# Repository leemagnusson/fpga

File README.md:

# fpga

Hobby FPGA projects, mostly targeting a Basys 3 board (Artix-7 `xc7a35tcpg236-1`).

| Directory    | What it is                                                     | Build                    |
|--------------|----------------------------------------------------------------|--------------------------|
| `bml1/ch4`   | LED shift register built from UNISIM primitives (VHDL + Verilog) | `cd bml1/ch4 && ./go.sh` |
| `bml1/ch5`   | Same design in behavioural RTL with a 1 Hz pulse               | `cd bml1/ch5 && ./go.sh` |
| `bml1/seg`, `bml1/seg2` | Seven-segment display, switches and buttons (`seg2` counts button presses per second) | `cd bml1/seg2 && ./go.sh` |
| `can_timing` | CAN message timing model and `can_sim` testbench (sim only)    | Vivado project `can_timing/project_1` |
| `litefury_canfd` | CAN FD PCIe card on a LiteFury, SocketCAN via the mainline driver | `cd litefury_canfd && ./go.sh` (see its README) |
| `t1s_trigger` | 10BASE-T1S bus monitor with switch-selected scope trigger outputs, plus the KiCad tap Pmod | `cd t1s_trigger && ./go.sh` (see its README) |
| `src`        | Early BCD counter experiments (not currently building)         |                          |

`go.sh` runs `go.tcl` in Vivado batch mode: synthesis, place, route, reports,
bitstream, then `program.tcl` to load the board over JTAG. Set the `CI`
environment variable to skip the programming step:

```sh
CI=1 ./go.sh
```

## Continuous integration

Two GitHub Actions workflows live in `.github/workflows/`.

### `ci.yml` (runs everywhere, no setup)

Runs on GitHub-hosted runners in the `hdlc/ghdl:yosys` container and executes
`ci/check.sh`, which:

- synthesises `bml1/ch4` and `bml1/ch5` for Artix-7 with GHDL + Yosys
  (both the VHDL and the Verilog top), catching syntax, elaboration and
  non-synthesisable-construct errors;
- runs the `can_timing` testbench in GHDL for 2 ms;
- analyses the loose tutorial files in `bml1/`.

`ci/unisim_stub.vhd` provides behavioural stand-ins for the UNISIM primitives
used by `bml1/ch4` so GHDL can build it. The same script runs locally with:

```sh
docker run --rm -v "$PWD":/src -w /src hdlc/ghdl:yosys ci/check.sh
```

### `vivado.yml` (real Vivado flow, needs a self-hosted runner)

Vivado cannot run on GitHub-hosted runners, so this workflow runs each
project's `go.tcl` on a self-hosted runner, checks that `top.bit` was produced
and that timing was met, and uploads the bitstream and reports as artifacts.
Pull requests from forks never run on the self-hosted runner.

All Vivado invocations go through `ci/vivado.sh`, which runs Vivado natively
or inside a Docker image depending on the environment. It works on a dev
machine too:

```sh
cd bml1/ch5
../../ci/vivado.sh -mode batch -source go.tcl                                           # native
VIVADO_DOCKER_IMAGE=vivado-runtime:2026.1 ../../ci/vivado.sh -mode batch -source go.tcl   # Docker
```

#### Setting up a runner machine

A fresh Linux machine with sudo is enough. Four steps:

1. **Download the Vivado web installer** on that machine into `~/Downloads`:
   the Linux "Self Extracting Web Installer" (about 400 MB, AMD login
   required) from
   https://www.amd.com/en/support/downloads/adaptive-socs-and-fpgas/development-tools.html

2. **Get a runner registration token** from the repo on GitHub: Settings,
   Actions, Runners, "New self-hosted runner", then copy the value from the
   `./config.sh --token ...` line. It is a short-lived code for adding one
   runner, not a personal access token, and it expires after an hour, so
   fetch it right before step 3. With the `gh` CLI logged in:

   ```sh
   gh api -X POST repos/leemagnusson/fpga/actions/runners/registration-token --jq .token
   ```

3. **Run the bootstrap** on the machine:

   ```sh
   curl -fsSL https://raw.githubusercontent.com/leemagnusson/fpga/main/ci/runner/bootstrap.sh \
     | bash -s -- --token <registration token>
   ```

   It installs Docker and a few tools, clones this repo to `~/fpga`, installs
   a minimal Vivado (Artix-7 only, about 20 GB) to `~/Xilinx` from the web
   installer, builds the small `vivado-runtime` Docker image, and registers
   and starts the runner service with the `vivado` label. Expect three
   prompts: the sudo password, your AMD account e-mail and password (used
   once to create the installer's download token), and sudo again for the
   runner service. The Vivado download is the slow part. At the end the
   installer prints the machine's host ID for the next step.

4. **Licence and switch on.** Vivado 2026.1 needs its free BASIC licence
   file even for Artix-7, and it is node-locked, so each machine needs its
   own. Generate one for the printed host ID at the AMD licensing site and
   save it on the runner as `~/.Xilinx/Xilinx.lic`. Then set the repository
   variable `VIVADO_RUNNER` to `true` on GitHub (Settings, Secrets and
   variables, Actions, Variables) and push a commit or run the "Vivado
   build" workflow manually.

If the machine already has Vivado on its PATH, the bootstrap skips the
install and uses it. `ci/runner/install.sh --help` and
`ci/vivado-install/install.sh --help` describe the individual pieces for
doing it by hand.

#### Installing Vivado from the web, scripted

`ci/vivado-install/install.sh` drives the AMD web installer in batch mode and
installs the smallest useful Vivado: the 2026.1 "Vivado Design Suite" edition
with only the Artix-7 family, no DocNav, no Model Composer, no shortcuts. The
only manual parts are downloading the web installer and typing your AMD
account once.

```sh
ci/vivado-install/install.sh --installer ~/Downloads/FPGAs_AdaptiveSoCs_Unified_SDI_2026.1_*_Lin64.bin
```

Options: `--dest` (default `~/Xilinx`), `--devices "Artix-7 FPGAs,Spartan-7 FPGAs"`
(see `--list-devices` for the names), `--cable-drivers` for machines that
program boards, `--prepare-only` to stop after writing the config. For a
runner that should keep Vivado inside Docker instead of on the host,
`ci/docker/build.sh --web <installer>` runs the same install during an
image build; the installer comes in as a build context and the AMD token
as a build secret, so neither is stored in the image.

#### Option A: Vivado in Docker (recommended)

The runner machine needs Docker, with the runner's user in the `docker`
group. Build the image once on the runner:

```sh
ci/docker/build.sh
```

This builds `vivado-runtime:<version>`, a small Ubuntu 24.04 image with
Vivado's runtime libraries and locale. Vivado itself stays on the host and is
bind-mounted read-only into the container at run time, so nothing licensed is
copied into an image and there is no AMD installer or auth token to deal
with. The install root is found from `vivado` on PATH, or set `VIVADO_HOME`.
Because the container is Ubuntu 24.04, the `libncurses.so.5` start-up failure
on newer host distributions does not occur.

Vivado 2026.1 needs its free BASIC license file even for WebPACK parts. The
wrapper mounts `~/.Xilinx/Xilinx.lic` into the container automatically, or
set `VIVADO_LICENSE_FILE` to point at it. The container uses the host network
so a node-locked license still matches the host ID.

Then put `VIVADO_DOCKER_IMAGE=vivado-runtime:2026.1` in the runner's `.env`
file (per machine), or set it as a repository variable (applies to every
runner and overrides `.env`).

#### Option B: Vivado natively on the runner

Make sure `vivado` is on the runner service's `PATH`, or set the repository
variable `VIVADO_SETTINGS` to the path of Vivado's `settings64.sh`.

Note for Ubuntu newer than 24.04: Vivado 2026.1 does not recognise the OS and
fails at start-up with `libncurses.so.5: cannot open shared object file`,
while still exiting 0. Point it at its own bundled copy, for example in the
runner's `.env` file:

```sh
LD_LIBRARY_PATH=<vivado-install>/Vivado/lib/lnx64.o/Ubuntu/24
```

On such an OS Vivado also spills part of `/etc/os-release` into the comment
banner of every HDL file it generates, which breaks synthesis of block
designs with `syntax error near 'VERSION_ID'`. `litefury_canfd/go.tcl`
repairs the generated files (see `litefury_canfd/fix_banners.tcl`); the
other projects generate no HDL and are unaffected.

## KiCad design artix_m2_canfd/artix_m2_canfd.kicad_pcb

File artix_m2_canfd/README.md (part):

# artix_m2_canfd: M.2 2280 Artix-7 card with four CAN FD transceivers

A 22 x 80 mm M.2 key-M card (PCIe x4 Gen2) around an AMD Artix-7 XC7A50T
with four CAN FD transceivers, intended to run the `litefury_canfd` design
in this repo extended to four cores. The whole KiCad project is generated
by `gen/build.py`; edit the Python, not the KiCad files.

```
python3 gen/build.py          # regenerates *.kicad_sch, *.kicad_pcb, lib/, bom.csv
```

## Design

| Block | Part | Notes |
|---|---|---|
| FPGA | XC7A50T-2CSG325I | 15 x 15 mm, 0.8 mm BGA, 4 GTP transceivers. The XC7A35T (and smaller) in CSG325 is a drop-in; the 75T and 100T are not offered in CSG325 (DS180 table 5), and only CSG325 has GTPs and fits the 22 mm card |
| Host interface | M.2 2280 key M card edge | PCIe x4 to GTP bank 216, REFCLK AC-coupled to MGTREFCLK0, PERST# to an I/O, CLKREQ# tied low |
| CAN FD | 4 x MCP2542FD (DFN-8; MCP2562FD, MCP2558FD and TI TCAN1462V are pin-compatible) | 8 Mbit/s, 5 V supply with 3.3 V I/O, ESD diode and optional 120 ohm termination (DNP) per bus |
| CAN connectors | 2 x Hirose DF52-6S-0.8H | 1.5 mm high, at the far end either side of the mount notch; each carries two buses as CANH, CANL, GND |
| Configuration | W25Q128JV (WSON-8), QSPI x4, M[2:0] = 001 | Tag-Connect TC2050 pads for JTAG, no connector |
| Clock | 100 MHz 3.3 V oscillator (ECS-2520MV) on an MRCC pin | 200 MHz LVDS not needed; the FPGA design's clock wizard takes 100 MHz |
| VCCINT/VCCBRAM 1.0 V | TPS62823 buck, 3 A | first rail up |
| VCCAUX 1.8 V | TLV62569 buck, 2 A | enabled by the 1.0 V power-good |
| MGTAVCC 1.0 V, MGTAVTT 1.2 V | TLV75710 / TLV75512 LDOs from 1.8 V (TLV755xP and TLV757xP share a pinout) | low noise for the transceivers |
| VCCO 3.3 V | TPS22918 load switch from the M.2 3.3 V | enabled ~10 ms after 1.8 V, slew limited: gives the recommended VCCINT, VCCAUX, VCCO order |
| 5 V (CAN) | TPS61023 boost from 3.3 V | enabled with the 3.3 V rail |
| LEDs | 4 user (bank 34) + power | active low, 0402 |

The FPGA pin assignment is generated from the AMD package file
(`gen/data/xc7a50tcsg325pkg.txt`): PCIe lanes reversed on the GTP
channels, user I/O (12 CAN signals, 4 LEDs) on bank 34, the oscillator and
PERST# on bank 15 clock-capable pins, QSPI on the bank 14 configuration
pins. All I/O banks run at 3.3 V.

Stackup: 6 layers, 0.8 mm (M.2 requirement), signal / ground / power /
power / ground / signal, ENIG. The 0.8 mm BGA fans out with 0.2/0.45 mm
vias on the pad diagonals and 0.1 mm traces.

### M.2 pin mapping

From the PCIe M.2 specification rev 1.0, table 48 (socket 3, key M) and
figures 16/17. The table names pins from the host's side: `PETp/n` is the
host transmitter, so it connects to the FPGA receivers, and `PERp/n` (host
receiver) is driven by the FPGA transmitters through 100 nF AC coupling
capacitors on the card. REFCLK is AC coupled too. Pins 59-66 are the key.
The card-edge geometry (0.5 mm pitch, 38 top pads 2.0 mm long, 37 bottom
pads 2.5 mm long staggered by 0.25 mm, fingers centred on the 19.85 mm
wide connector tongue, pin 1 at the right in the top view, key slot
1.2 x 3.5 mm next to pin 75, 3.5 mm semicircular mount notch centred on
the far edge) is in `gen/footprints.py` (`M2_*` constants) and the outline
in `gen/pcb.py`.

## Routing flow

The generator places parts and draws the planes; `gen/route.py` then does
all the copper itself (no external autorouter):

```sh
python3 gen/build.py                 # regenerate schematic, board, libraries (stops if a part does not fit its zone)
python3 gen/route.py route           # BGA escapes, plane vias, gen/router.py for everything else,
                                     #   then KiCad's DRC in a loop until it reports nothing (about 2 minutes)
kicad-cli pcb drc --severity-all artix_m2_canfd.kicad_pcb     # 0 violations, 0 unconnected
```

`gen/escape.py` takes every used BGA ball to a via one pitch outside the
package: outer ring straight out on the top layer, second ring through the
free row gap, deeper balls on the bottom layer along the pad-row/column
lines. The receive pairs are planned as pairs and leave the bottom row in
M.2 finger order (lane 0 west ... lane 3 east), REFCLK between lanes 0 and
1. `gen/fanout.py` adds a via to its plane beside every supply pad.

`gen/router.py` is a grid router (0.1 mm lattice, A* over F.Cu and B.Cu)
that works in this order:

1. **PCIe pairs** as pairs: one search for the centreline, P and N offset
   0.125 mm either side (0.1 mm tracks, 0.15 mm gap), symmetric lead-ins,
   via pairs at a layer change, 0.3 mm kept to the next pair. Receive pairs
   run straight to the fingers on F.Cu; the transmit pairs come down the east
   edge on B.Cu, cross under the receive pairs and surface at their
   capacitors. Each pair is then length-matched with small bumps on the
   shorter half (all within 0.1 mm; the 1.6 mm that the ring-1/ring-2
   transmit balls differ by inside the package is made up outside it).
2. **Supplies**: pads the fan-out could not stitch, and the two
   transceiver-rail corner islands under the GTP balls, are joined to their
   planes.
3. **Local power links**: every regulator and transceiver supply pin goes
   straight to its capacitor or inductor on the same layer with the fattest
   track that fits (exact geometry, 0.25-0.8 mm), switch nodes included, so
   no decoupling loop runs through two vias and a plane.
4. **Signals**, short nets first, with rip-up and retry.
5. KiCad's DRC is run on the saved board; anything it reports (a via the
   plane fill did not reach, a track a few microns close to a round pad) is
   mended and the DRC run again until it is clean.

Planes (6 layers, 0.8 mm): L2 and L5 ground. L3 is 3.3 V from the package
upwards; below it and along the two long edges L3 carries the transceiver
rails (MGTAVCC west, MGTAVTT east), each a strip from its LDO down to a
block under its decoupling, plus the island under the GTP balls that the
router links to the block. L4 is 1.8 V with a 1.0 V strip from the core
balls up to the buck, the 3.3 V input under the fingers and up both long
edges to the regulators, and 5 V at the CAN end. A 0.3 mm keep-out ring
keeps routed copper off the board edge.

### PCIe lane and polarity assignment (matters for the FPGA constraints)

The M.2 lanes are **reversed** on the GTP quad and the **transmit pairs
are polarity-swapped**, so that nothing has to cross on the board:

| M.2 lane | GTP channel | RX balls (P/N) | TX balls carrying PERp/PERn |
|---|---|---|---|
| 0 | 3 (MGTP*3_216) | G4 / G3 | B1 (MGTPTXN3) / B2 (MGTPTXP3) |
| 1 | 2 | C4 / C3 | D1 (MGTPTXN2) / D2 (MGTPTXP2) |
| 2 | 1 | A4 / A3 | F1 (MGTPTXN1) / F2 (MGTPTXP1) |
| 3 | 0 | E4 / E3 | H1 (MGTPTXN0) / H2 (MGTPTXP0) |

`python3 gen/xdc.py` writes the Vivado constraints for all FPGA pins from
the routed board into `../litefury_canfd/constraints/artix_m2*.xdc` (build
with `BOARD=artix_m2`, see that README); `--check` reports drift. It places
lane n's GTPE2_CHANNEL on channel 3-n with a LOC constraint.
The transmit polarity needs nothing: the host's receivers detect and
correct an inverted lane during link training (PCIe base spec, lane
polarity inversion). REFCLK is on MGTREFCLK0 (D6/D5), not inverted.

## Fabrication and assembly

### PCBWay

```sh
python3 gen/pcbway.py            # build/pcbway/artix_m2_canfd.zip: gerbers, drills, IPC-356 netlist,
                                 #   BOM, pick-and-place, fab notes (PCBWay's plugin format)
python3 gen/pcbway.py --upload   # ... and upload it; prints and opens the PCBWay quote page
python3 gen/pcbway.py --quote    # price table for the options in PCB_SPEC (needs PCBWAY_API_KEY)
python3 gen/pcbway.py --order 10 # ten boards with those options into your PCBWay cart (needs the key)
```

`gen/pcbway.py` writes the same package as PCBWay's KiCad plugin and uses
the same anonymous upload endpoint, so the quote page comes up with the
files attached; log in there, pick the options the script prints (6 layers,
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
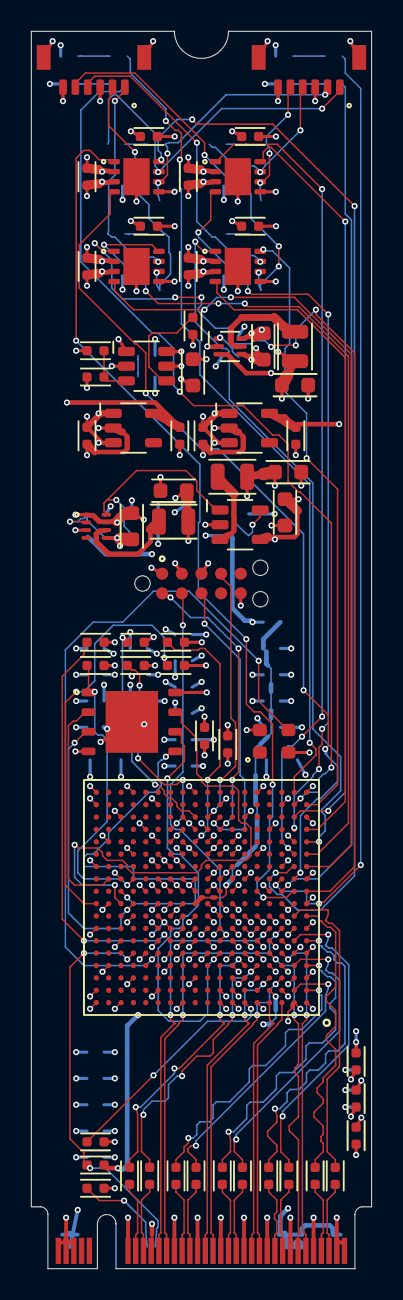
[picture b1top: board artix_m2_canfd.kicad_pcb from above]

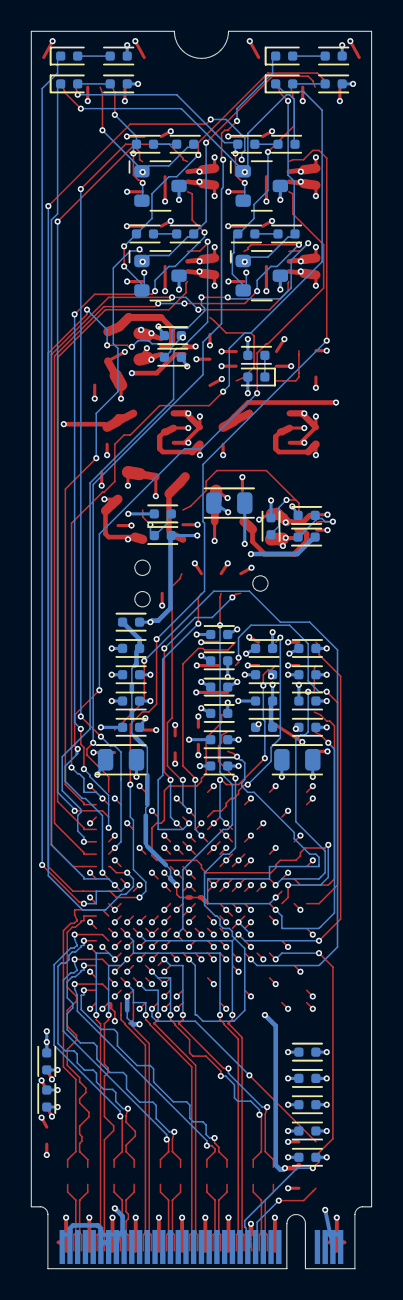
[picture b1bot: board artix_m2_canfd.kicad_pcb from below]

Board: 6 copper layers, 22.0 x 80.0 mm, 124 parts (58 on the bottom side), 98 nets.

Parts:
C1, C2, C3, C4, C5, C6, C7, C8, C9, C10, C11, C12, C34, C35, C36, C37, C38, C39, C42, C52, C57, C58, C59, C60, C61, C62, C63, C64: 100n; C_0402
C13, C14, C20, C24, C25, C26, C27, C32, C33, C40, C41: 4u7; C_0402
C15, C16, C17, C18, C21, C22, C28, C29, C30, C31: 470n; C_0402
C19, C23, C45: 47u; C_0805
C43, C46, C54, C55, C56: 10u; C_0603
C44, C47: 22u; C_0603
C48, C49, C50, C51: 1u; C_0402
C53: 1n; C_0402
D1, D2, D3, D4, D5: LED green; LED_0402
D10, D11, D12, D13: PESD2CAN; SOT-23
FB1: 600R@100MHz; FB_0402
J1: M.2 2280 key M; M2_Edge_2280_KeyM
J2: TC2050 JTAG; TagConnect_TC2050-NL
J3, J4: DF52-6S-0.8H; Hirose_DF52-6S-0.8H
L1: 470nH; L_0806
L2, L3: 1uH; L_0806
R1, R24, R26, R28, R30: 0R; R_0402
R2: 10k; R_0402
R3: 100R; R_0402
R4, R5, R6, R7, R8, R9: 4k7; R_0402
R10, R11, R12, R13, R20: 1k; R_0402
R14: 68k; R_0402
R15, R16, R18, R19, R22: 100k; R_0402
R17: 200k; R_0402
R21: 732k; R_0402
R23, R25, R27, R29: 120R; R_0402
U1: XC7A50T-2CSG325I; Xilinx_CSG325
U2: W25Q128JVPIQ; WSON-8_6x5mm_P1.27mm
U3: TPS62823DLCR; VSON-8_2x1.5mm_P0.5mm
U4: TLV62569DBVR; SOT-23-5
U5: TLV75710PDBVR; SOT-23-5
U6: TLV75512PDBVR; SOT-23-5
U7: TPS22918DBVR; SOT-23-6
U8: TPS61023DRLR; SOT-563
U10, U11, U12, U13: MCP2542FD; DFN-8_3x3mm_P0.65mm
X1: 100 MHz 3.3V; Oscillator_2520_4pin

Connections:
CAN0_H: D10.1, J3.1, R23.1, U10.7
CAN0_L: D10.2, J3.2, R24.2, U10.6
CAN0_RXD: U1.M1, U10.4
CAN0_STBY: U1.N1, U10.8
CAN0_TERM: R23.2, R24.1
CAN0_TXD: U1.K1, U10.1
CAN1_H: D11.1, J3.4, R25.1, U11.7
CAN1_L: D11.2, J3.5, R26.2, U11.6
CAN1_RXD: U1.R1, U11.4
CAN1_STBY: U1.U1, U11.8
CAN1_TERM: R25.2, R26.1
CAN1_TXD: U1.P1, U11.1
CAN2_H: D12.1, J4.1, R27.1, U12.7
CAN2_L: D12.2, J4.2, R28.2, U12.6
CAN2_RXD: U1.L2, U12.4
CAN2_STBY: U1.M2, U12.8
CAN2_TERM: R27.2, R28.1
CAN2_TXD: U1.K2, U12.1
CAN3_H: D13.1, J4.4, R29.1, U13.7
CAN3_L: D13.2, J4.5, R30.2, U13.6
CAN3_RXD: U1.R2, U13.4
CAN3_STBY: U1.T2, U13.8
CAN3_TERM: R29.2, R30.1
CAN3_TXD: U1.N2, U13.1
CFG_M0: R5.1, U1.R12
CLK100M: U1.E13, X1.3
CT_3V3: C53.1, U7.4
DONE: R7.1, U1.F12
EN_3V3: C52.1, R19.2, U7.3
FB_1V0: R14.2, R15.1, U3.2
FB_1V8: R17.2, R18.1, U4.5
FB_5V: R21.2, R22.1, U8.1
GND: C11.2, C12.2, C13.2, C14.2, C15.2, C16.2, C17.2, C18.2, C19.2, C20.2, C21.2, C22.2, C23.2, C24.2, C25.2, C26.2, C27.2, C28.2, C29.2, C30.2, C31.2, C32.2, C33.2, C34.2, C35.2, C36.2, C37.2, C38.2, C39.2, C40.2, C41.2, C42.2, C43.2, C44.2, C45.2, C46.2, C47.2, C48.2, C49.2, C50.2, C51.2, C52.2, C53.2, C54.2, C55.2, C56.2, C57.2, C58.2, C59.2, C60.2, C61.2, C62.2, C63.2, C64.2, D10.3, D11.3, D12.3, D13.3, J1.1, J1.3, J1.9, J1.15, J1.21, J1.27, J1.33, J1.39, J1.45, J1.51, J1.57, J1.71, J1.73, J1.75, J2.3, J2.5, J2.10, J3.3, J3.6, J3.MP, J4.3, J4.6, J4.MP, R1.2, R3.2, R15.2, R18.2, R20.2, R22.2, U1.A1, U1.A5, U1.A7, U1.A8, U1.A11, U1.A18, U1.B3, U1.B7, U1.B8, U1.B18, U1.C2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
INIT_B: R8.1, U1.T10
JTAG_TCK: J2.4, U1.F8
JTAG_TDI: J2.7, U1.T9
JTAG_TDO: J2.6, U1.T8
JTAG_TMS: J2.2, U1.R8
LED0_A: D1.2, R10.1
LED0_N: D1.1, U1.U2
LED1_A: D2.2, R11.1
LED1_N: D2.1, U1.V2
LED2_A: D3.2, R12.1
LED2_N: D3.1, U1.K3
LED3_A: D4.2, R13.1
LED3_N: D4.1, U1.L3
MGTAVCC: C32.1, C33.1, C34.1, C35.1, C36.1, C49.1, U1.B4, U1.C5, U1.E5, U1.F5, U5.5
MGTAVTT: C37.1, C38.1, C39.1, C40.1, C41.1, C51.1, U1.A2, U1.C1, U1.E1, U1.F3, U1.G2, U6.5
MGTRREF: R3.1, U1.A6
PCIE_CLKREQ_N: J1.52, R1.1
PCIE_PERST_N: J1.50, R2.1, U1.E15
PCIE_REFCLK_N: C10.1, U1.D5
PCIE_REFCLK_N_C: C10.2, J1.53
PCIE_REFCLK_P: C9.1, U1.D6
PCIE_REFCLK_P_C: C9.2, J1.55
PCIE_RX0_N: J1.47, U1.G3
PCIE_RX0_P: J1.49, U1.G4
PCIE_RX1_N: J1.35, U1.C3
PCIE_RX1_P: J1.37, U1.C4
PCIE_RX2_N: J1.23, U1.A3
PCIE_RX2_P: J1.25, U1.A4
PCIE_RX3_N: J1.11, U1.E3
PCIE_RX3_P: J1.13, U1.E4
PCIE_TX0_N: C2.1, U1.B2
PCIE_TX0_N_C: C2.2, J1.41
PCIE_TX0_P: C1.1, U1.B1
PCIE_TX0_P_C: C1.2, J1.43
PCIE_TX1_N: C4.1, U1.D2
PCIE_TX1_N_C: C4.2, J1.29
PCIE_TX1_P: C3.1, U1.D1
PCIE_TX1_P_C: C3.2, J1.31
PCIE_TX2_N: C6.1, U1.F2
PCIE_TX2_N_C: C6.2, J1.17
PCIE_TX2_P: C5.1, U1.F1
PCIE_TX2_P_C: C5.2, J1.19
PCIE_TX3_N: C8.1, U1.H2
PCIE_TX3_N_C: C8.2, J1.5
PCIE_TX3_P: C7.1, U1.H1
PCIE_TX3_P_C: C7.2, J1.7
PG_1V0: R16.1, U3.8, U4.1
PROGRAM_B: R9.1, U1.P10
PUDC_B: R6.1, U1.J18
PWR_LED_K: D5.1, R20.1
QSPI_CLK: U1.E8, U2.6
QSPI_CS_N: R4.1, U1.L15, U2.1
QSPI_IO0: U1.K16, U2.5
QSPI_IO1: U1.L17, U2.2
QSPI_IO2: U1.J15, U2.3
QSPI_IO3: U1.J16, U2.7
SW_1V0: L1.1, U3.6
SW_1V8: L2.1, U4.3
SW_5V: L3.2, U8.5
VCC1V0: C13.1, C14.1, C15.1, C16.1, C17.1, C18.1, C44.1, C45.1, L1.2, R14.1, U1.F7, U1.F9, U1.F11, U1.G8, U1.G10, U1.H7, U1.H9, U1.H11, U1.J8, U1.J12, U1.K7, U1.K11, U1.L8, U1.L12, U1.M7, U1.M11, U1.N8, U1.N10, U1.N12, U1.P9, U1.P11
VCC1V8: C19.1, C20.1, C21.1, C22.1, C47.1, C48.1, C50.1, FB1.1, L2.2, R17.1, R19.1, U1.E11, U1.G12, U1.H13, U1.K13, U1.M13, U1.P13, U5.1, U5.3, U6.1, U6.3
VCC3V3: C11.1, C12.1, C23.1, C24.1, C25.1, C26.1, C27.1, C28.1, C29.1, C30.1, C31.1, C54.1, C58.1, C60.1, C62.1, C64.1, D5.2, J2.1, R2.2, R4.2, R5.2, R6.2, R7.2, R8.2, R9.2, R10.2, R11.2, R12.2, R13.2, U1.A16, U1.B13, U1.C10, U1.D17, U1.E10, U1.E12, U1.E14, U1.G18, U1.H15, U1.L6, U1.L16, U1.M3, U1.P7, U1.P17, U1.R4, U1.R10, U1.R14, U1.T1, U1.T11, U1.U8, U1.U18, U1.V5, U1.V15, U2.8, U7.5, U7.6, U8.2, U10.5, U11.5, U12.5, U13.5, X1.4
VCC5V_CAN: C56.1, C57.1, C59.1, C61.1, C63.1, R21.1, U8.6, U10.3, U11.3, U12.3, U13.3
VCCADC: C42.1, FB1.2, U1.J10
VIN_3V3: C43.1, C46.1, C55.1, J1.2, J1.4, J1.12, J1.14, J1.16, J1.18, J1.70, J1.72, J1.74, L3.1, R16.2, U3.1, U3.7, U4.4, U7.1, U8.3

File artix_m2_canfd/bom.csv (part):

Reference,Value,MPN,Footprint,Description,DNP
C1,"100n","GRM155R71C104KA88D","artix_m2_canfd:C_0402","Capacitor 100n 16V 0402",
C2,"100n","GRM155R71C104KA88D","artix_m2_canfd:C_0402","Capacitor 100n 16V 0402",
C3,"100n","GRM155R71C104KA88D","artix_m2_canfd:C_0402","Capacitor 100n 16V 0402",
C4,"100n","GRM155R71C104KA88D","artix_m2_canfd:C_0402","Capacitor 100n 16V 0402",
C5,"100n","GRM155R71C104KA88D","artix_m2_canfd:C_0402","Capacitor 100n 16V 0402",
C6,"100n","GRM155R71C104KA88D","artix_m2_canfd:C_0402","Capacitor 100n 16V 0402",
C7,"100n","GRM155R71C104KA88D","artix_m2_canfd:C_0402","Capacitor 100n 16V 0402",
C8,"100n","GRM155R71C104KA88D","artix_m2_canfd:C_0402","Capacitor 100n 16V 0402",
C9,"100n","GRM155R71C104KA88D","artix_m2_canfd:C_0402","Capacitor 100n 16V 0402",
C10,"100n","GRM155R71C104KA88D","artix_m2_canfd:C_0402","Capacitor 100n 16V 0402",
C11,"100n","GRM155R71C104KA88D","artix_m2_canfd:C_0402","Capacitor 100n  0402",
C12,"100n","GRM155R71C104KA88D","artix_m2_canfd:C_0402","Capacitor 100n  0402",
C13,"4u7","GRM155R60J475ME47D","artix_m2_canfd:C_0402","Capacitor 4u7  0402",
C14,"4u7","GRM155R60J475ME47D","artix_m2_canfd:C_0402","Capacitor 4u7  0402",
C15,"470n","GRM155R61A474KE15D","artix_m2_canfd:C_0402","Capacitor 470n  0402",
C16,"470n","GRM155R61A474KE15D","artix_m2_canfd:C_0402","Capacitor 470n  0402",
C17,"470n","GRM155R61A474KE15D","artix_m2_canfd:C_0402","Capacitor 470n  0402",
C18,"470n","GRM155R61A474KE15D","artix_m2_canfd:C_0402","Capacitor 470n  0402",
C19,"47u","GRM21BR60J476ME15L","artix_m2_canfd:C_0805","Capacitor 47u  0805",
C20,"4u7","GRM155R60J475ME47D","artix_m2_canfd:C_0402","Capacitor 4u7  0402",
C21,"470n","GRM155R61A474KE15D","artix_m2_canfd:C_0402","Capacitor 470n  0402",
C22,"470n","GRM155R61A474KE15D","artix_m2_canfd:C_0402","Capacitor 470n  0402",
C23,"47u","GRM21BR60J476ME15L","artix_m2_canfd:C_0805","Capacitor 47u  0805",
C24,"4u7","GRM155R60J475ME47D","artix_m2_canfd:C_0402","Capacitor 4u7  0402",
C25,"4u7","GRM155R60J475ME47D","artix_m2_canfd:C_0402","Capacitor 4u7  0402",
C26,"4u7","GRM155R60J475ME47D","artix_m2_canfd:C_0402","Capacitor 4u7  0402",
C27,"4u7","GRM155R60J475ME47D","artix_m2_canfd:C_0402","Capacitor 4u7  0402",
C28,"470n","GRM155R61A474KE15D","artix_m2_canfd:C_0402","Capacitor 470n  0402",
C29,"470n","GRM155R61A474KE15D","artix_m2_canfd:C_0402","Capacitor 470n  0402",
C30,"470n","GRM155R61A474KE15D","artix_m2_canfd:C_0402","Capacitor 470n  0402",
C31,"470n","GRM155R61A474KE15D","artix_m2_canfd:C_0402","Capacitor 470n  0402",
C32,"4u7","GRM155R60J475ME47D","artix_m2_canfd:C_0402","Capacitor 4u7  0402",
C33,"4u7","GRM155R60J475ME47D","artix_m2_canfd:C_0402","Capacitor 4u7  0402",
C34,"100n","GRM155R71C104KA88D","artix_m2_canfd:C_0402","Capacitor 100n  0402",
C35,"100n","GRM155R71C104KA88D","artix_m2_canfd:C_0402","Capacitor 100n  0402",
C36,"100n","GRM155R71C104KA88D","artix_m2_canfd:C_0402","Capacitor 100n  0402",
C37,"4u7","GRM155R60J475ME47D","artix_m2_canfd:C_0402","Capacitor 4u7  0402",
C38,"4u7","GRM155R60J475ME47D","artix_m2_canfd:C_0402","Capacitor 4u7  0402",
C39,"100n","GRM155R71C104KA88D","artix_m2_canfd:C_0402","Capacitor 100n  0402",
C40,"100n","GRM155R71C104KA88D","artix_m2_canfd:C_0402","Capacitor 100n  0402",
C41,"100n","GRM155R71C104KA88D","artix_m2_canfd:C_0402","Capacitor 100n  0402",
C42,"100n","GRM155R71C104KA88D","artix_m2_canfd:C_0402","Capacitor 100n  0402",
C43,"10u","GRM188R61A106KE69D","artix_m2_canfd:C_0603","Capacitor 10u 10V 0603",
C44,"22u","GRM188R60J226MEA0D","artix_m2_canfd:C_0603","Capacitor 22u 6.3V 0603",
C45,"47u","GRM21BR60J476ME15L","artix_m2_canfd:C_0805","Capacitor 47u 6.3V 0805",
C46,"10u","GRM188R61A106KE69D","artix_m2_canfd:C_0603","Capacitor 10u 10V 0603",
C47,"22u","GRM188R60J226MEA0D","artix_m2_canfd:C_0603","Capacitor 22u 6.3V 0603",
C48,"1u","GRM155R61A105KE15D","artix_m2_canfd:C_0402","Capacitor 1u 10V 0402",
C49,"1u","GRM155R61A105KE15D","artix_m2_canfd:C_0402","Capacitor 1u 10V 0402",
C50,"1u","GRM155R61A105KE15D","artix_m2_canfd:C_0402","Capacitor 1u 10V 0402",
C51,"1u","GRM155R61A105KE15D","artix_m2_canfd:C_0402","Capacitor 1u 10V 0402",
C52,"100n","GRM155R71C104KA88D","artix_m2_canfd:C_0402","Capacitor 100n  0402",
C53,"1n","GRM1555C1H102JA01D","artix_m2_canfd:C_0402","Capacitor 1n  0402",
C54,"10u","GRM188R61A106KE69D","artix_m2_canfd:C_0603","Capacitor 10u 10V 0603",
C55,"10u","GRM188R61A106KE69D","artix_m2_canfd:C_0603","Capacitor 10u 10V 0603",
C56,"10u","GRM188R61A106KE69D","artix_m2_canfd:C_0603","Capacitor 10u 10V 0603",
C57,"100n","GRM155R71C104KA88D","artix_m2_canfd:C_0402","Capacitor 100n  0402",
C58,"100n","GRM155R71C104KA88D","artix_m2_canfd:C_0402","Capacitor 100n  0402",
C59,"100n","GRM155R71C104KA88D","artix_m2_canfd:C_0402","Capacitor 100n  0402",
C60,"100n","GRM155R71C104KA88D","artix_m2_canfd:C_0402","Capacitor 100n  0402",
C61,"100n","GRM155R71C104KA88D","artix_m2_canfd:C_0402","Capacitor 100n  0402",
C62,"100n","GRM155R71C104KA88D","artix_m2_canfd:C_0402","Capacitor 100n  0402",
C63,"100n","GRM155R71C104KA88D","artix_m2_canfd:C_0402","Capacitor 100n  0402",
C64,"100n","GRM155R71C104KA88D","artix_m2_canfd:C_0402","Capacitor 100n  0402",
D1,"LED green","16-213/GHC-YR1S1/3T","artix_m2_canfd:LED_0402","LED green 0402",
D2,"LED green","16-213/GHC-YR1S1/3T","artix_m2_canfd:LED_0402","LED green 0402",
D3,"LED green","16-213/GHC-YR1S1/3T","artix_m2_canfd:LED_0402","LED green 0402",
D4,"LED green","16-213/GHC-YR1S1/3T","artix_m2_canfd:LED_0402","LED green 0402",
D5,"LED green","16-213/GHC-YR1S1/3T","artix_m2_canfd:LED_0402","LED green 0402",
D10,"PESD2CAN","PESD2CAN,215","artix_m2_canfd:SOT-23","CAN bus ESD protection",
D11,"PESD2CAN","PESD2CAN,215","artix_m2_canfd:SOT-23","CAN bus ESD protection",
D12,"PESD2CAN","PESD2CAN,215","artix_m2_canfd:SOT-23","CAN bus ESD protection",
D13,"PESD2CAN","PESD2CAN,215","artix_m2_canfd:SOT-23","CAN bus ESD protection",
FB1,"600R@100MHz","BLM15AG601SN1D","artix_m2_canfd:FB_0402","Ferrite bead 0402",
J1,"M.2 2280 key M","","artix_m2_canfd:M2_Edge_2280_KeyM","M.2 card edge, 2280, key M (PCIe x4 + 3.3 V)",
J2,"TC2050 JTAG","","artix_m2_canfd:TagConnect_TC2050-NL","Tag-Connect TC2050 JTAG pads, no part fitted (cable TC2050-IDC-NL; Xilinx: VREF, TMS, GND, TCK, GND, TDO, TDI)",
J3,"DF52-6S-0.8H","DF52-6S-0.8H(21)","artix_m2_canfd:Hirose_DF52-6S-0.8H","CAN buses 0 and 1: H, L, GND each; 0.8 mm wire-to-board, 1.5 mm tall",
J4,"DF52-6S-0.8H","DF52-6S-0.8H(21)","artix_m2_canfd:Hirose_DF52-6S-0.8H","CAN buses 2 and 3: H, L, GND each; 0.8 mm wire-to-board, 1.5 mm tall",
L1,"470nH","TFM201610ALMA-R47MTAA","artix_m2_canfd:L_0806","Inductor 470nH 2016",
L2,"1uH","TFM201610ALMA-1R0MTAA","artix_m2_canfd:L_0806","Inductor 1uH 2016",
L3,"1uH","TFM201610ALMA-1R0MTAA","artix_m2_canfd:L_0806","Inductor 1uH 2016",
R1,"0R","RC0402JR-070RL","artix_m2_canfd:R_0402","Resistor 0R 0402",
R2,"10k","RC0402FR-0710KL","artix_m2_canfd:R_0402","Resistor 10k 0402",
R3,"100R","RC0402FR-07100RL","artix_m2_canfd:R_0402","Resistor 100R 0402",
R4,"4k7","RC0402FR-074K7L","artix_m2_canfd:R_0402","Resistor 4k7 0402",
R5,"4k7","RC0402FR-074K7L","artix_m2_canfd:R_0402","Resistor 4k7 0402",
R6,"4k7","RC0402FR-074K7L","artix_m2_canfd:R_0402","Resistor 4k7 0402",
R7,"4k7","RC0402FR-074K7L","artix_m2_canfd:R_0402","Resistor 4k7 0402",
R8,"4k7","RC0402FR-074K7L","artix_m2_canfd:R_0402","Resistor 4k7 0402",
R9,"4k7","RC0402FR-074K7L","artix_m2_canfd:R_0402","Resistor 4k7 0402",
R10,"1k","RC0402FR-071KL","artix_m2_canfd:R_0402","Resistor 1k 0402",
R11,"1k","RC0402FR-071KL","artix_m2_canfd:R_0402","Resistor 1k 0402",
R12,"1k","RC0402FR-071KL","artix_m2_canfd:R_0402","Resistor 1k 0402",
R13,"1k","RC0402FR-071KL","artix_m2_canfd:R_0402","Resistor 1k 0402",
R14,"68k","RC0402FR-0768KL","artix_m2_canfd:R_0402","Resistor 68k 0402",
R15,"100k","RC0402FR-07100KL","artix_m2_canfd:R_0402","Resistor 100k 0402",
R16,"100k","RC0402FR-07100KL","artix_m2_canfd:R_0402","Resistor 100k 0402",
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
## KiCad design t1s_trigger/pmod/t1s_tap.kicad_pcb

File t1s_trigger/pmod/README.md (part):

# 10BASE-T1S tap Pmod

A small Pmod module that lets the Basys 3 listen to a 10BASE-T1S bus and
brings four trigger outputs to connectors. KiCad 9 project, two layers,
20 x 46 mm.

```
T1S bus (A/B) --> J2 screw terminal / J3 header --> U1 RS-485 receiver -------------> RX  --> Pmod IO1  (low: line negative)
                                   |---------------> U2 RS-485 receiver, A/B swapped --> RXN --> Pmod IO10 (low: line positive)
                                   |- JP1 (shunt) + R1: optional 100 R termination
FPGA TRIG0..3 --> Pmod IO2,IO3,IO4,IO7 --> 33 R --> J5 header; TRIG0 also --> 49.9 R --> J4 SMA
```

The receivers are 3.3 V, 50 Mbit/s RS-485 transceivers used receive-only:
high-impedance differential inputs with a wide common-mode range and a
fail-safe output (idle bus reads as logic 1), which is what a passive monitor
tap needs. The 10BASE-T1S differential Manchester signal has at most one edge
every 40 ns, well inside a 50 Mbit/s part. There are two of them because one
cannot tell idle from positive: the fail-safe thresholds sit at about -20 and
-200 mV, so the output only changes when the line crosses about -0.1 V. U2 has
A and B swapped and so only reacts to crossings of about +0.1 V. Together they
give the FPGA three states, negative (RX low), positive (RXN low) and idle
(both high), and every transition on the wire, including the first one out of
idle whichever polarity it has, asserts exactly one of the two outputs. U1's
driver is held off by R4 unless the FPGA drives IO8 high; `IO9` is the driver
data pin so the board can inject test patterns if you ever want to (not T1S
compliant levels). U2's driver pins are grounded.

## Files

| File | What |
|------|------|
| `t1s_tap.kicad_pro`, `t1s_tap.kicad_sch`, `t1s_tap.kicad_pcb` | the KiCad 9 project |
| `t1s_tap.kicad_sym`, `sym-lib-table` | project symbol library (transceiver symbol) |
| `tools/netlist.py` | the circuit as data: parts, footprints, pin to net. Schematic and board are both generated from it |
| `tools/gen_sch.py`, `tools/gen_pcb.py` | generators (schematic as s-expressions, board through the pcbnew API) |
| `tools/build.sh` | regenerates everything and runs ERC, DRC, schematic parity, a pad/net cross-check and all exports |
| `tools/pcbway_quote.sh` | uploads the gerber zip (or, with `assembly`, gerbers + BOM + placement) to PCBWay and prints a link to a pre-filled instant quote |
| `tools/pcbway_files.py` | writes `out/PCBWay_bom.csv`, `out/PCBWay_positions.csv` (the layout PCBWay's KiCad plugin uses) and `out/t1s_tap_assembly.zip` |
| `3dmodels/` | STEP models for every part (copied from kicad-packages3D, CC-BY-SA 4.0); the board references them as `${KIPRJMOD}/3dmodels/` so the 3D view works without the global library |
| `out/` | ERC and DRC reports (JSON), schematic PDF/SVG, board SVG and PNG renders, 3D renders (`pcb_3d.png`, `pcb_3d_rear.png`), `t1s_tap.step` (board with components, for mechanical checks), `bom.csv` (with manufacturer part numbers), `positions.csv`, `gerbers/`, `t1s_tap_gerbers.zip` and `t1s_tap_assembly.zip` |

Everything runs in the `kicad/kicad:9.0` Docker image, no local KiCad needed:

```sh
tools/build.sh
```

## Pmod pinout (J1)

Standard 12-pin Pmod, 3.3 V. Pmod pins 1 to 6 are the upper row, 7 to 12 the
lower row. Looking at the module with the header pointing away from you and
components up, pin 1 is at the **right** end of the upper row and pin 6 at the
left (Digilent Pmod Interface Specification 1.3.1, figure 2; Basys 3 reference
manual figure 20 shows the matching socket, front view, pin 1 top right). The
KiCad footprint numbers its pads the other way round, pad 1 at the left in that
view, so `tools/netlist.py` maps Pmod pin *n* to pad 13-2*n* (pins 1 to 6) and
26-2*n* (pins 7 to 12), and `gen_pcb.py` moves the square pad and the pin-1
tick to Pmod pin 1. Rev A had the header mirrored; plugged into a Basys 3 it
would have put 3.3 V and ground on JA signal pins.

| Pmod pin | Signal | Direction (FPGA) | Note |
|---------:|--------|------------------|------|
| 1 (IO1)  | RX     | in  | U1 output: low while the line is negative, idles high |
| 2 (IO2)  | TRIG0  | out | to J5 pin 1 via 33 R and to J4 SMA via 49.9 R |
| 3 (IO3)  | TRIG1  | out | to J5 pin 2 via 33 R |
| 4 (IO4)  | TRIG2  | out | to J5 pin 3 via 33 R |
| 5        | GND    |     | |
| 6        | VCC    |     | 3.3 V from the host |
| 7 (IO7)  | TRIG3  | out | to J5 pin 4 via 33 R |
| 8 (IO8)  | DE     | out | driver enable, 10 k pull-down, leave low or unused |
| 9 (IO9)  | TXD    | out | driver data (only matters with DE high) |
| 10 (IO10)| RXN    | in  | U2 output: low while the line is positive, idles high |
| 11       | GND    |     | |
| 12       | VCC    |     | 3.3 V |

On the Basys 3 header JA this is JA1 = RX, JA2 = TRIG0, JA3 = TRIG1,
JA4 = TRIG2, JA7 = TRIG3, JA8 = DE, JA9 = TXD, JA10 = RXN.

**Check pin 1 before plugging in.** The silkscreen marks Pmod pin 1 (square
pad with a tick) and pins 6, 7 and 12 at the row ends. Hold the module next to
the Basys 3 JA socket and confirm the square pad lines up with the socket's
pin 1 (the Basys 3 silkscreen marks it); the right-angle header can be soldered
on either face, and a module plugged in upside down puts 3.3 V on signal pins.

## Other connectors

| Ref | What | Pins |
|-----|------|------|
| J2  | 3.5 mm screw terminal | 1 = A, 2 = B (10BASE-T1S pair) |
| J3  | 1x3 0.1" header, same bus in parallel | 1 = A, 2 = B, 3 = GND |
| J4  | SMA, edge mount | TRIG0 through 49.9 R, use a 50 R scope input or a 1 M input (then you get the full 3.3 V) |
| J5  | 1x5 0.1" header | 1 = TRIG0, 2 = TRIG1, 3 = TRIG2, 4 = TRIG3, 5 = GND, each through 33 R |
| JP1 | 1x2 0.1" header + shunt | shunt fitted: 100 R (R1) across A/B. Ship without the shunt |
| D1  | green LED | lit while the bus is active (RX low), dark when silent |

## Bill of materials

| Ref | Value | Package | Example part | Notes |
|-----|-------|---------|--------------|-------|
| U1, U2 | SN65HVD78 | SOIC-8 | TI SN65HVD78D | 3.3 V, 50 Mbps, fail-safe RS-485. Alternatives with the same pinout: ADI ADM3065EARZ, Maxim MAX22500EASA. Do not fit a 5 V-only or 500 kbps part. Fit the same part in both places |
| C1, C2 | 100 nF | 0603 | any X7R 16 V | decoupling |
| R1 | 100 R | 0603 | 1 % | termination, only with JP1 closed |
| R2 | 49.9 R | 0603 | 1 % | SMA source termination |
| R3 | 1 k | 0603 | | LED |
| R4 | 10 k | 0603 | | DE pull-down |
| R5 to R8 | 33 R | 0603 | | trigger series resistors |
| D1 | green | 0603 LED | | activity |
| J1 | 2x6 right-angle male 0.1" | | e.g. Sullins PRPC006DBAN-M71 or any 2x6 right angle | Pmod plug |
| J2 | 2-pos 3.5 mm screw terminal | | Phoenix PT 1,5/2-3,5-H (1984617) | bus |
| J3 | 1x3 male 0.1" | | | bus, header |
| J4 | SMA edge mount | | Amphenol 132289 | TRIG0 |
| J5 | 1x5 male 0.1" | | | triggers |
| JP1 | 1x2 male 0.1" | | Sullins PRPC002SAAN-RC plus a 2.54 mm shunt, e.g. Sullins SPC02SYAN | termination select |

`out/bom.csv` is the machine-generated version (the shunt for JP1 is a loose
part and not in it).

## Assembly and use

- **Keep the stub short.** 10BASE-T1S nodes hang off the mixing segment on
  stubs of a few centimetres at most. Wire J2 or J3 to the bus with the
  shortest twisted pair you can, ideally directly at a bus connector or at
  the end node. The tap adds roughly 30 pF (two receiver inputs) plus the
  stub to the bus.
- **Termination.** A 10BASE-T1S mixing segment has exactly two 100 R
  terminations, one at each end; everything else hangs off it on short stubs.
  Leave the JP1 shunt off unless this module *is* one end of the bus on your
  bench, then fit it. A third termination in the middle halves the signal and
  reflects.
- **Coupling.** Real nodes sit on the bus through 100 nF series capacitors
  on both wires (Microchip AN1718 bus interface network, OPEN Alliance
  10BASE-T1S implementation specification), and the end terminations are
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
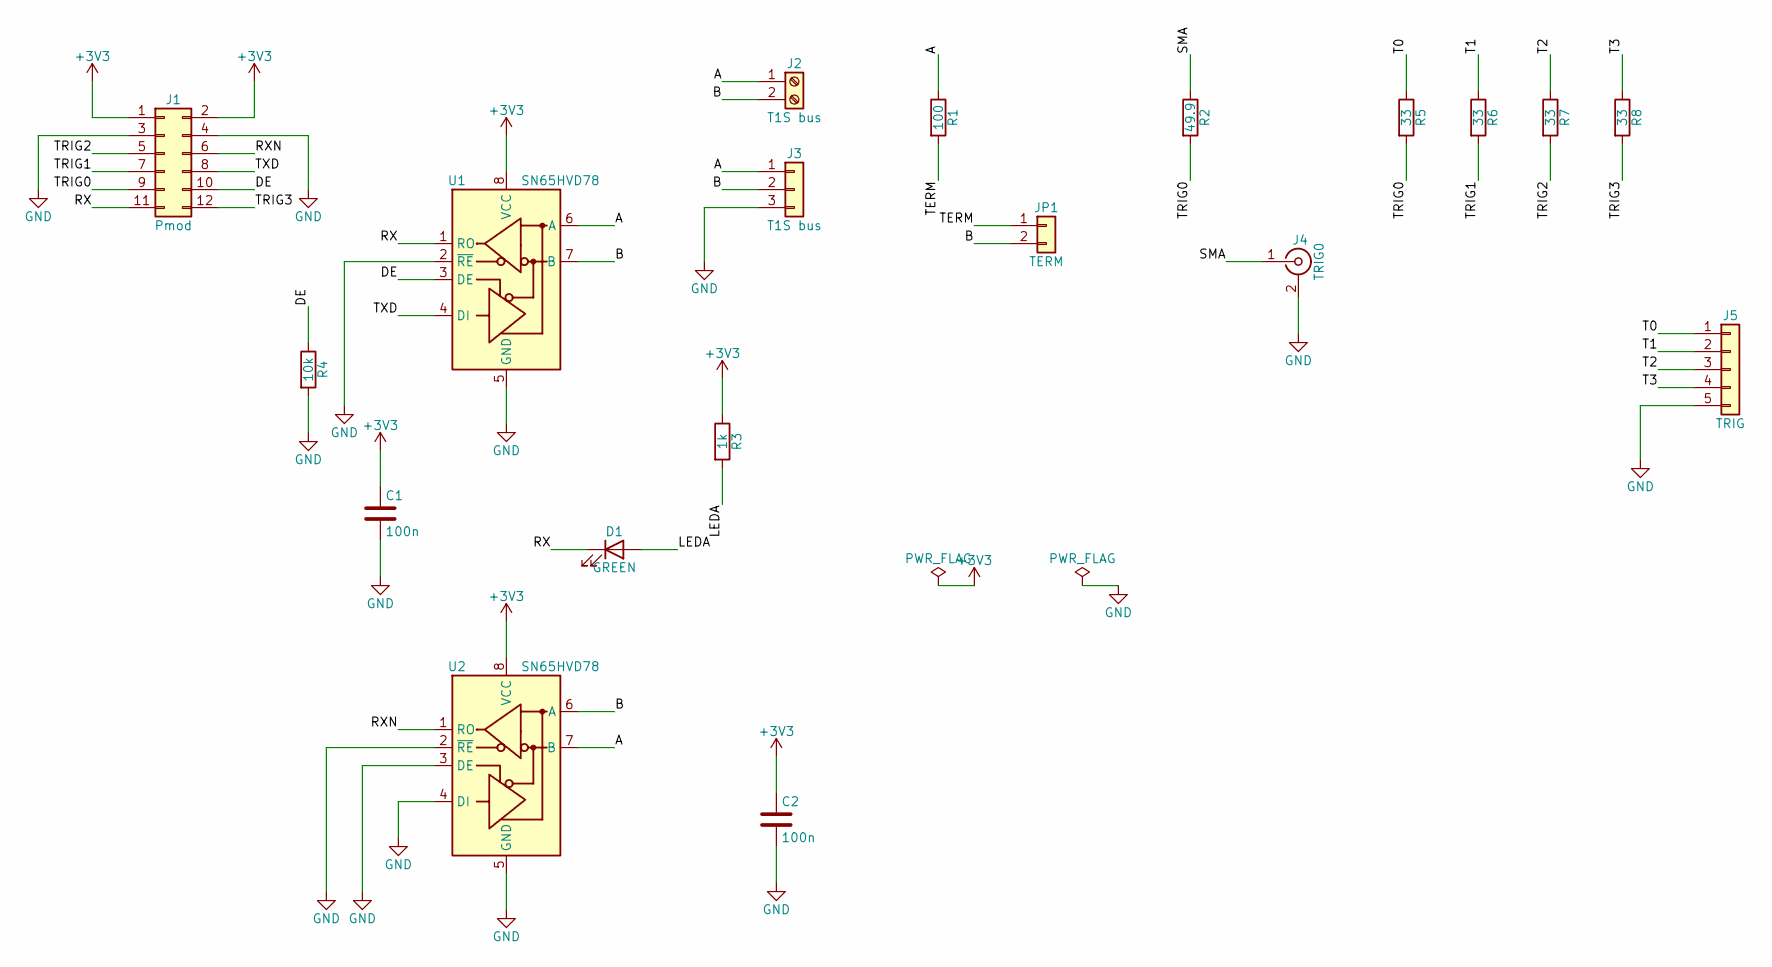
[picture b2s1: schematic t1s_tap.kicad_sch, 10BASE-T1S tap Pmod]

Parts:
C1, C2: 100n; C_0603_1608Metric; MPN CC0603KRX7R9BB104
D1: GREEN; LED_0603_1608Metric; MPN APT1608SGC
J1: Pmod; PinHeader_2x06_P2.54mm_Horizontal; MPN PRPC006DBAN-M71
J2: T1S bus; TerminalBlock_Phoenix_PT-1,5-2-3.5-H_1x02_P3.50mm_Horizontal; MPN 1984617
J3: T1S bus; PinHeader_1x03_P2.54mm_Vertical; MPN PRPC003SAAN-RC
J4: TRIG0; SMA_Amphenol_132289_EdgeMount; MPN 132289
J5: TRIG; PinHeader_1x05_P2.54mm_Vertical; MPN PRPC005SAAN-RC
JP1: TERM; PinHeader_1x02_P2.54mm_Vertical; MPN PRPC002SAAN-RC
R1: 100; R_0603_1608Metric; MPN RC0603FR-07100RL
R2: 49.9; R_0603_1608Metric; MPN RC0603FR-0749R9L
R3: 1k; R_0603_1608Metric; MPN RC0603FR-071KL
R4: 10k; R_0603_1608Metric; MPN RC0603FR-0710KL
R5, R6, R7, R8: 33; R_0603_1608Metric; MPN RC0603FR-0733RL
U1, U2: SN65HVD78; SOIC-8_3.9x4.9mm_P1.27mm; MPN SN65HVD78D

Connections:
+3V3: C1.1, C2.1, J1.1, J1.2, R3.1, U1.8 (VCC), U2.8 (VCC)
/A: J2.1, J3.1, R1.1, U1.6 (A), U2.7 (B)
/B: J2.2, J3.2, JP1.2, U1.7 (B), U2.6 (A)
/DE: J1.10, R4.1, U1.3 (DE)
/LEDA: D1.2 (A), R3.2
/RX: D1.1 (K), J1.11, U1.1 (RO)
/RXN: J1.6, U2.1 (RO)
/SMA: J4.1 (In), R2.1
/T0: J5.1, R5.1
/T1: J5.2, R6.1
/T2: J5.3, R7.1
/T3: J5.4, R8.1
/TERM: JP1.1, R1.2
/TRIG0: J1.9, R2.2, R5.2
/TRIG1: J1.7, R6.2
/TRIG2: J1.5, R7.2
/TRIG3: J1.12, R8.2
/TXD: J1.8, U1.4 (DI)
GND: C1.2, C2.2, J1.3, J1.4, J3.3, J4.2 (Ext), J5.5, R4.2, U1.2 (~RE), U1.5 (GND), U2.2 (~RE), U2.3 (DE), U2.4 (DI), U2.5 (GND)

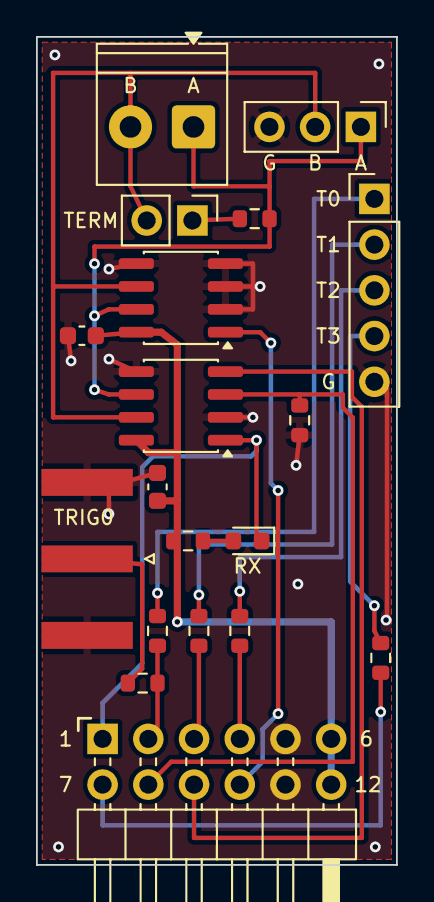
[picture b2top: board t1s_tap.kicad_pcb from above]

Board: 2 copper layers, 20.0 x 46.0 mm, 19 parts (0 on the bottom side), 19 nets.

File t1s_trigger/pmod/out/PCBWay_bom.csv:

Designator,Quantity,Value,Footprint,Package,MPN,Manufacturer,Mount_Type,Description
U1,1,SN65HVD78,SOIC-8_3.9x4.9mm_P1.27mm,,SN65HVD78D,Texas Instruments,smt,3.3 V 50 Mbps half-duplex RS-485 transceiver (alt. ADM3065E)
C1,1,100n,C_0603_1608Metric,,CC0603KRX7R9BB104,Yageo,smt,decoupling
R1,1,100,R_0603_1608Metric,,RC0603FR-07100RL,Yageo,smt,optional bus termination (with JP1)
R2,1,49.9,R_0603_1608Metric,,RC0603FR-0749R9L,Yageo,smt,SMA source termination
R3,1,1k,R_0603_1608Metric,,RC0603FR-071KL,Yageo,smt,activity LED
R4,1,10k,R_0603_1608Metric,,RC0603FR-0710KL,Yageo,smt,driver off by default
"R5, R6, R7, R8",4,33,R_0603_1608Metric,,RC0603FR-0733RL,Yageo,smt,
D1,1,GREEN,LED_0603_1608Metric,,APT1608SGC,Kingbright,smt,lit while the line is active
J1,1,Pmod,PinHeader_2x06_P2.54mm_Horizontal,,PRPC006DBAN-M71,Sullins,tht,Pmod host connector (right angle male)
J2,1,T1S bus,"TerminalBlock_Phoenix_PT-1,5-2-3.5-H_1x02_P3.50mm_Horizontal",,1984617,Phoenix Contact,tht,10BASE-T1S pair
J3,1,T1S bus,PinHeader_1x03_P2.54mm_Vertical,,PRPC003SAAN-RC,Sullins,tht,"10BASE-T1S pair, header"
J4,1,TRIG0,SMA_Amphenol_132289_EdgeMount,,132289,Amphenol RF,smt,trigger 0 to scope
J5,1,TRIG,PinHeader_1x05_P2.54mm_Vertical,,PRPC005SAAN-RC,Sullins,tht,trigger outputs

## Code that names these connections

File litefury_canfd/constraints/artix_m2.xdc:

# GENERATED by artix_m2_canfd/gen/xdc.py from the routed board: do not edit.
# artix_m2_canfd card (XC7A50T-2CSG325I) pins. Processed after the IP constraints (PROCESSING_ORDER LATE).

## 100 MHz oscillator on an MRCC pin (the block design creates the clock)
set_property -dict {PACKAGE_PIN E13 IOSTANDARD LVCMOS33} [get_ports sys_clk]

## PCIe reset from the M.2 connector
set_property -dict {PACKAGE_PIN E15 IOSTANDARD LVCMOS33} [get_ports pcie_perst_n]
set_false_path -from [get_ports pcie_perst_n]

## User LEDs (active low: 1k to 3.3 V)
set_property -dict {PACKAGE_PIN U2  IOSTANDARD LVCMOS33 DRIVE 8} [get_ports {leds[0]}]
set_property -dict {PACKAGE_PIN V2  IOSTANDARD LVCMOS33 DRIVE 8} [get_ports {leds[1]}]
set_property -dict {PACKAGE_PIN K3  IOSTANDARD LVCMOS33 DRIVE 8} [get_ports {leds[2]}]
set_property -dict {PACKAGE_PIN L3  IOSTANDARD LVCMOS33 DRIVE 8} [get_ports {leds[3]}]

## CAN transceivers (MCP2542FD), one per CAN core. With CAN_CORES < 4 the design holds the
## spare ones recessive and in standby; their RXD pins are then unused (pulled up, see UNUSEDPIN).
set_property -dict {PACKAGE_PIN K1  IOSTANDARD LVCMOS33 DRIVE 8 SLEW FAST} [get_ports can0_tx]
set_property -dict {PACKAGE_PIN M1  IOSTANDARD LVCMOS33 PULLUP true} [get_ports can0_rx]
set_property -dict {PACKAGE_PIN N1  IOSTANDARD LVCMOS33 DRIVE 8} [get_ports can0_stby]
set_property -dict {PACKAGE_PIN P1  IOSTANDARD LVCMOS33 DRIVE 8 SLEW FAST} [get_ports can1_tx]
set_property -dict {PACKAGE_PIN R1  IOSTANDARD LVCMOS33 PULLUP true} [get_ports can1_rx]
set_property -dict {PACKAGE_PIN U1  IOSTANDARD LVCMOS33 DRIVE 8} [get_ports can1_stby]
set_property -dict {PACKAGE_PIN K2  IOSTANDARD LVCMOS33 DRIVE 8 SLEW FAST} [get_ports can2_tx]
set_property -dict {PACKAGE_PIN L2  IOSTANDARD LVCMOS33 PULLUP true} [get_ports can2_rx]
set_property -dict {PACKAGE_PIN M2  IOSTANDARD LVCMOS33 DRIVE 8} [get_ports can2_stby]
set_property -dict {PACKAGE_PIN N2  IOSTANDARD LVCMOS33 DRIVE 8 SLEW FAST} [get_ports can3_tx]
set_property -dict {PACKAGE_PIN R2  IOSTANDARD LVCMOS33 PULLUP true} [get_ports can3_rx]
set_property -dict {PACKAGE_PIN T2  IOSTANDARD LVCMOS33 DRIVE 8} [get_ports can3_stby]
set_false_path -to   [get_ports {can*_tx can*_stby leds[*]}]
set_false_path -from [get_ports -quiet can*_rx]

## Configuration: QSPI x4 from the W25Q128JV, internal config clock, compressed bitstream
## (fast enough for PCIe to enumerate). Banks 0 and 14 are at 3.3 V.
set_property BITSTREAM.CONFIG.OVERTEMPPOWERDOWN ENABLE [current_design]
set_property BITSTREAM.CONFIG.CONFIGRATE 33 [current_design]
set_property BITSTREAM.CONFIG.SPI_BUSWIDTH 4 [current_design]
set_property CONFIG_MODE SPIx4 [current_design]
set_property BITSTREAM.CONFIG.SPI_FALL_EDGE YES [current_design]
set_property BITSTREAM.GENERAL.COMPRESS TRUE [current_design]
set_property BITSTREAM.CONFIG.UNUSEDPIN PULLUP [current_design]
set_property CONFIG_VOLTAGE 3.3 [current_design]
set_property CFGBVS VCCO [current_design]

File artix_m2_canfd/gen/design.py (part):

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       [(1, "EN", "PG_1V0", "L"), (2, "GND", GND, "L"), (3, "SW", "SW_1V8", "L"), (4, "VIN", V3IN, "R"), (5, "FB", "FB_1V8", "R")],
       "power", "TLV62569DBVR", "2 A synchronous buck, 1.8 V VCCAUX")
    C(d, "10u", V3IN, GND, "power", "GRM188R61A106KE69D", size="0603", voltage="10V", rel=(2.9, -0.8, 270, "F"))   # at VIN (pin 4)
    L(d, "1uH", "SW_1V8", V18, "power", "TFM201610ALMA-1R0MTAA", rel=(-0.5, -3.1, 0, "F"))                         # SW end under pin 3
    C(d, "22u", V18, GND, "power", "GRM188R60J226MEA0D", size="0603", voltage="6.3V", rel=(3.1, -3.4, 0, "F"))     # beside L's output end
    R(d, "200k", V18, "FB_1V8", "power", rel=(0.0, 0.7, 0, "B"))
    R(d, "100k", "FB_1V8", GND, "power", rel=(0.0, -0.7, 0, "B"))
    # MGT rails from 1.8 V: 1.0 V and 1.2 V fixed LDOs
    ic(d, "U5", "TLV75710PDBVR", "TLV755P", fp("SOT-23-5"),
       [(1, "IN", V18, "L"), (2, "GND", GND, "L"), (3, "EN", V18, "L"), (4, "NC", None, "R"), (5, "OUT", AVCC, "R")],
       "power", "TLV75710PDBVR", "1 A LDO, 1.0 V MGTAVCC (TLV75510PDBVR pin-compatible)")
    C(d, "1u", V18, GND, "power", voltage="10V", rel=(-3.0, 0.5, 270, "F"))
    C(d, "1u", AVCC, GND, "power", voltage="10V", rel=(3.0, 0.5, 270, "F"))
    ic(d, "U6", "TLV75512PDBVR", "TLV755P", fp("SOT-23-5"),
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       [(1, "VIN", V3IN, "L"), (2, "GND", GND, "L"), (3, "ON", "EN_3V3", "L"), (4, "CT", "CT_3V3", "R"), (5, "QOD", V3, "R"), (6, "VOUT", V3, "R")],
       "power", "TPS22918DBVR", "2 A load switch, sequenced 3.3 V for VCCO/flash/CAN logic")
    R(d, "100k", V18, "EN_3V3", "power", rel=(-3.3, 0.7, 0, "F"))
    C(d, "100n", "EN_3V3", GND, "power", rel=(-3.3, -1.0, 180, "F"))           # ~10 ms delay after 1.8 V; EN end at ON (pin 3)
    C(d, "1n", "CT_3V3", GND, "power", rel=(3.0, -2.6, 270, "F"))              # slew ~ 1 ms; CT end at pin 4
    C(d, "10u", V3, GND, "power", "GRM188R61A106KE69D", size="0603", voltage="10V", rel=(3.0, 0.4, 270, "F"))   # at VOUT (pin 6)
    LED(d, "green", "PWR_LED_K", V3, "power", "16-213/GHC-YR1S1/3T", rel=(0.0, 0.7, 0, "B"))
    R(d, "1k", "PWR_LED_K", GND, "power", rel=(0.0, -0.7, 0, "B"))
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
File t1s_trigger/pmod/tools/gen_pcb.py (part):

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# down the edge to a via below the T3 via, where the bottom pour is continuous
track('GND', [('J5', '5'), (119.45, 119.16), (119.45, 132.4), (119.4, 132.4)])
# ---- receivers / LED
# RX (line negative, U1): Pmod pin 1 is the bottom-left pad. Bottom layer up the strip between the SMA ground
# pads and the trigger resistors, across under U1, then a via next to U1 pin 1. The LED hangs off the same via.
track('RX', [('J1', '11'), (103.65, 137.0), (105.85, 134.8), (105.85, 123.9), (106.45, 123.3), (111.9, 123.3),
             (112.2, 123.0), (112.2, 122.405)], B)
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track('RX', [(112.2, 122.405), ('U1', '1')])
track('RX', [(112.2, 122.405), (112.2, 128.0), ('D1', '1')])
track('LEDA', [('R3', '2'), ('D1', '2')])
# RXN (line positive, U2): bottom layer past U1's right-hand pins (DE/TXD leave U1 to the right on top),
# top layer down to the header, bottom layer between the header pads into Pmod pin 10.
track('RXN', [('U2', '1'), (112.4, 116.405), (113.0, 117.0)])
via('RXN', 113.0, 117.0)
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track('T1', [(109.0, 131.0), (109.0, 128.2), (116.4, 128.2), (116.4, 111.54), ('J5', '2')], B)
via('T2', 111.27, 130.8); track('T2', [('R7', '1'), (111.27, 130.8)])
track('T2', [(111.27, 130.8), (111.27, 128.9), (116.9, 128.9), (116.9, 114.08), ('J5', '3')], B)
# TRIG3 (Pmod pin 7, bottom-left pad) runs along the bottom edge on the bottom layer to R8 at the right edge
track('TRIG3', [('J1', '12'), (103.65, 143.8), (119.1, 143.8), (119.1, 137.5)], B)
via('TRIG3', 119.1, 137.5); track('TRIG3', [(119.1, 137.5), ('R8', '2')])
via('T3', 118.75, 131.6); track('T3', [('R8', '1'), (118.75, 133.0), (118.75, 131.6)])
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
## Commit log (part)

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2024-12-27 bcd_counter
2024-12-27 bml tutorlial work
2025-01-08 add gitignore
2025-03-26 can timing sim
